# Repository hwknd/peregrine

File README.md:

# Peregrine (work in progress)

A split steno keyboard that (will hopefully) work with Plover.

# 01.  Ergogen

Start designing both halves in Ergogen https://ergogen.cache.works/
I went with a left half and a right half because that made life a lot easier in kiCAD.

peregrine-lefty.yaml

peregrine-righty.yaml

# 02. Export that to a KiCAD board 

> ergogen peregrine-lefty.yaml -o peregrinelefty
> 
> ergogen peregrine-righty.yaml -o peregrinerighty

# 0.3 Edit the board in KiCAD 

I am using a different switch so replaced the one ergogen gave me with a footprint that matches the AliExpress one. It's in footprints\AliExpressResetButton6x45xH.kicad_mod 
And this is the switch https://nl.aliexpress.com/item/1005006195785196.html . I don't have it yet so I don't yet know if it actually works.

Also clicked until all the connections were there and KiCAD was showing 0 errors.

- TODO: there are some warnings about the silkprint overlapping...somthing? for the ProMicro microcontroller. Not sure if I can ignore those.

- TODO: Check if I did anything stupid that will mean it instantly shorts out as soon as I connect it.

# 04. Firmware

- TODO: figure out how to write the firmware to make it work, and to make it work with Plover

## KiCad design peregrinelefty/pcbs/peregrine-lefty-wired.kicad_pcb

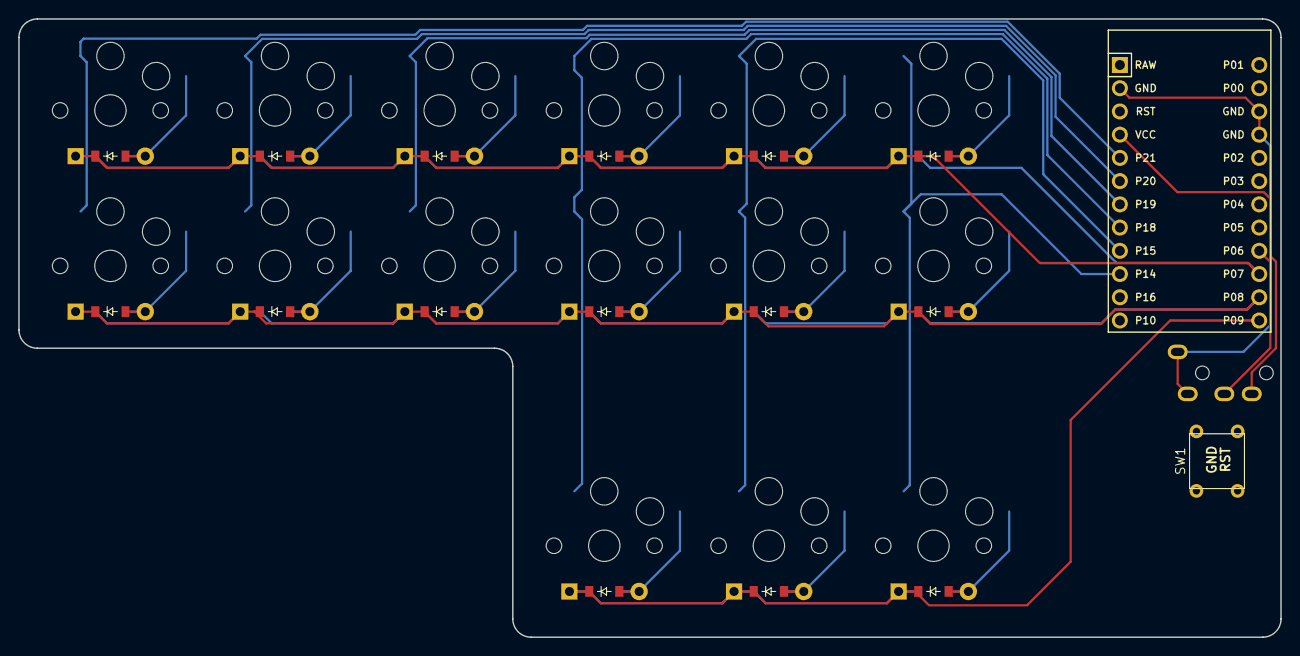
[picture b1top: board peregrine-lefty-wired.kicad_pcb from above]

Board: 2 copper layers, 138.0 x 67.6 mm, 33 parts (0 on the bottom side), 27 nets.

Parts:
D1, D2, D3, D4, D5, D6, D7, D8, D9, D10, D11, D12, D13, D14, D15: ComboDiode
MCU1: ProMicro
S1, S2, S3, S4, S5, S6, S7, S8, S9, S10, S11, S12, S13, S14, S15: PG1350
SW1: TactileSW; AliExpressResetButton6x45xH
TRRS1: TRRS-PJ-320A-dual

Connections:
GND: MCU1.2, MCU1.15, MCU1.16, TRRS1.1, TRRS1.2
P6: MCU1.21, TRRS1.3
P7: D2.1, D4.1, D6.1, D9.1, D12.1, D15.1, MCU1.22
P8: D1.1, D3.1, D5.1, D8.1, D11.1, D14.1, MCU1.23
P9: D7.1, D10.1, D13.1, MCU1.24
P14: MCU1.10, S13.1, S14.1, S15.1
P15: MCU1.9, S10.1, S11.1, S12.1
P18: MCU1.8, S7.1, S8.1, S9.1
P19: MCU1.7, S5.1, S6.1
P20: MCU1.6, S3.1, S4.1
P21: MCU1.5, S1.1, S2.1
VCC: MCU1.4, TRRS1.4
five_bottom: D10.2, S10.2
five_middle: D11.2, S11.2
five_top: D12.2, S12.2
four_bottom: D7.2, S7.2
four_middle: D8.2, S8.2
four_top: D9.2, S9.2
one_middle: D1.2, S1.2
one_top: D2.2, S2.2
six_bottom: D13.2, S13.2
six_middle: D14.2, S14.2
six_top: D15.2, S15.2
three_middle: D5.2, S5.2
three_top: D6.2, S6.2
two_middle: D3.2, S3.2
two_top: D4.2, S4.2

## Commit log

2025-02-24 Trigger GitHub update
